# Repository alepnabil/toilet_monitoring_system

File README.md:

This system is a custom IoT monitoring solution built on a 2-layer PCB.

Hardware & Sensing Core
The core hardware is centered around an Arduino Nano, which serves as the main microcontroller.

Air Quality: The MQ-135 sensor continuously measures air quality, providing data crucial for cleanliness assessment.

Usage Tracking: The HC-SR04 ultrasonic sensor is employed to accurately count people, gathering real-time usage statistics.

Data Transmission: A 433MHz RF module enables reliable, low-power transmission of all sensor data to a centralized receiving system.

# 3d view of PCB

# Schematic

# Power plane view

# Groud plane view

# PCB 3d casing

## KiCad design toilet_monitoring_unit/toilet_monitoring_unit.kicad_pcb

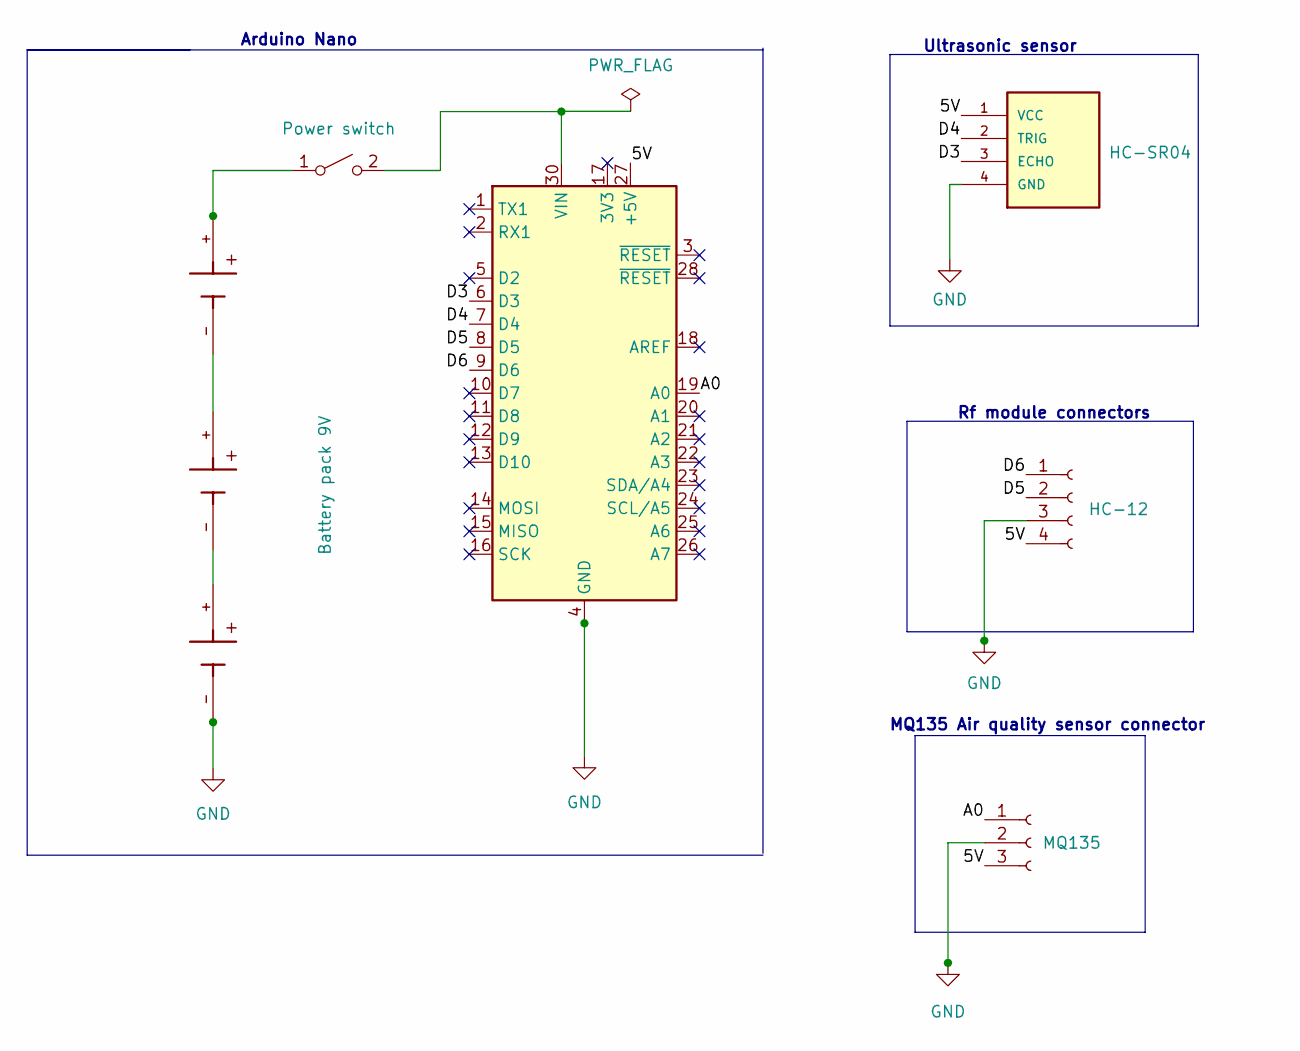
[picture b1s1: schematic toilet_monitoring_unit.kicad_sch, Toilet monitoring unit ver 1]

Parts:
A1: Arduino_Nano_Every; Arduino_Nano
BT1, BT5: Battery pack 3.7v; BAT_BC2AAPC; PARTREV M
BT4: Battery pack 9V; BAT_BC2AAPC; PARTREV M
J1: MQ135; PinSocket_1x03_P2.54mm_Vertical
J3: HC-12; PinSocket_1x04_P2.54mm_Vertical
SW2: Power switch; SW_E-Switch_EG1224_SPDT_Angled
U1: HC-SR04; XCVR_HC-SR04

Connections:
/5V: A1.27 (+5V), J1.3, J3.4, U1.1 (VCC)
/A0: A1.19 (A0), J1.1
/D3: A1.6 (D3), U1.3 (ECHO)
/D4: A1.7 (D4), U1.2 (TRIG)
/D5: A1.8 (D5), J3.2
/D6: A1.9 (D6), J3.1
GND: A1.4 (GND), A1.29 (GND), BT5.-, J1.2, J3.3, U1.4 (GND)
unnamed: A1.30 (VIN), SW2.2 (B)
unnamed: BT1.-, BT4.+
unnamed: BT4.-, BT5.+
unnamed: BT1.+, SW2.1 (A)

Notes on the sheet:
Rf module connectors
Arduino Nano
MQ135 Air quality sensor connector
Ultrasonic sensor

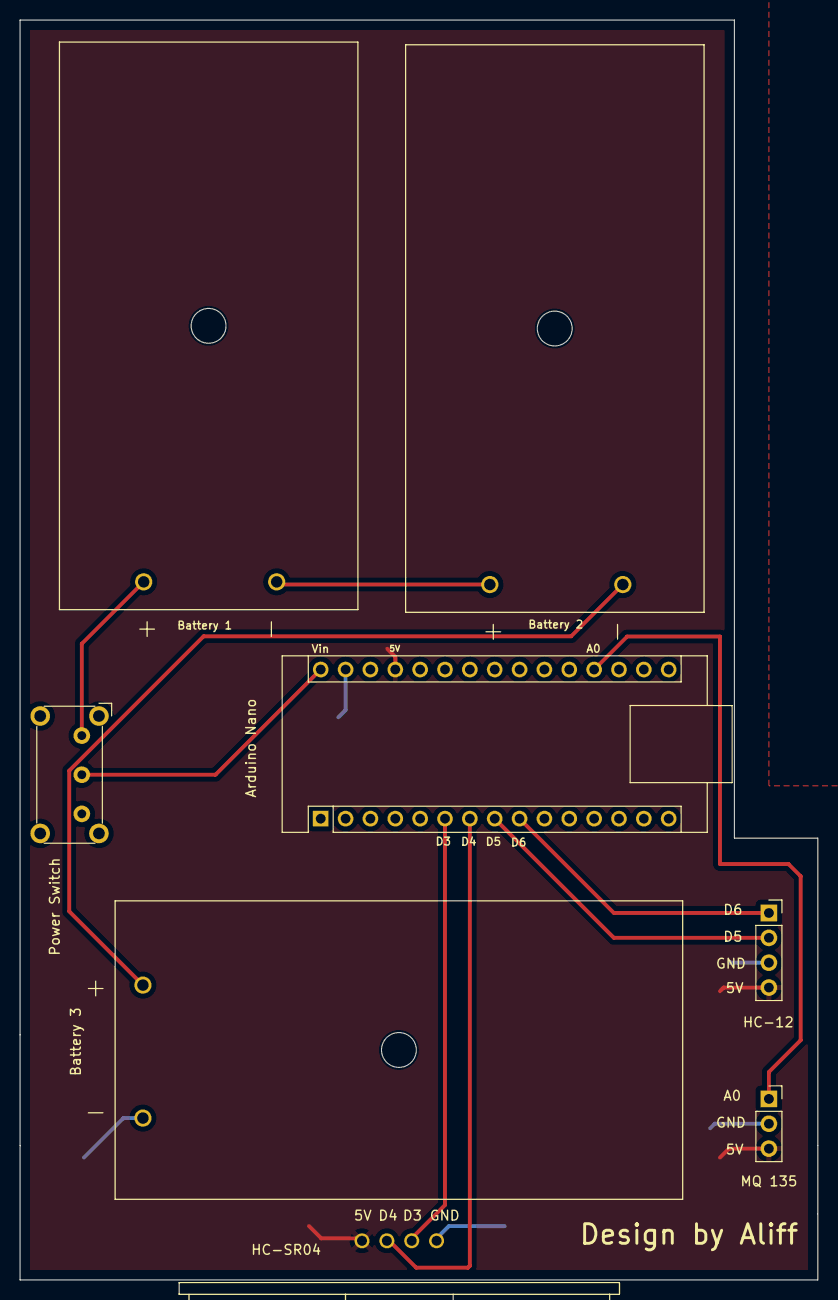
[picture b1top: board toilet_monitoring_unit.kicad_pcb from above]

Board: 2 copper layers, 81.5 x 128.8 mm, 8 parts (0 on the bottom side), 11 nets.

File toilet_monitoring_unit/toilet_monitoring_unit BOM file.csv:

Date:,27/5/2024 16:18,,,,,,
Tool:,Eeschema 7.0.10,,,,,,
Component Count:,8,,,,,,
Ref,Qnty,Value,Cmp name,Footprint,Description,Vendor,DNP
A1,1,Arduino_Nano_Every,Arduino_Nano_Every,Module:Arduino_Nano,Arduino Nano ,,
"BT1, BT5",2,Battery pack 3.7v ,BC2AAPC,Battery holder:BAT_BC2AAPC,To insert 1.5v battery ,,
BT4,1,Battery pack 3.7v ,BC2AAPC,Battery holder:BAT_BC2AAPC,To insert 1.5v battery ,,
J1,1,MQ135,Conn_01x03_Socket,Connector_PinSocket_1.00mm:PinSocket_1x03_P1.00mm_Vertical,"Generic connector, single row, 01x03, script generated",,
J3,1,HC-12,Conn_01x04_Socket,Connector_PinSocket_1.00mm:PinSocket_1x04_P1.00mm_Vertical,"Generic connector, single row, 01x04, script generated",,
SW2,1,Power switch,SW_SPST,Button_Switch_THT:SW_E-Switch_EG1224_SPDT_Angled,Single Pole Single Throw (SPST) switch,,
U1,1,HC-SR04,HC-SR04,HC-SR04:XCVR_HC-SR04,Ultrasonic sensor,,

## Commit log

2025-09-26 add pcb gerber files
2025-09-26 added pcb files and main app file
2025-09-26 add kicad pcb filles
